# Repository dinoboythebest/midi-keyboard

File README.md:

# midi-keyboard
A musical keyboard madde by tamilore adeabjo
added 3 led and 3 buttons on the bottom , though no graphics.
made a cool lighting design with the 7 keys provided and used the XIAO ESP32-S3 BOard

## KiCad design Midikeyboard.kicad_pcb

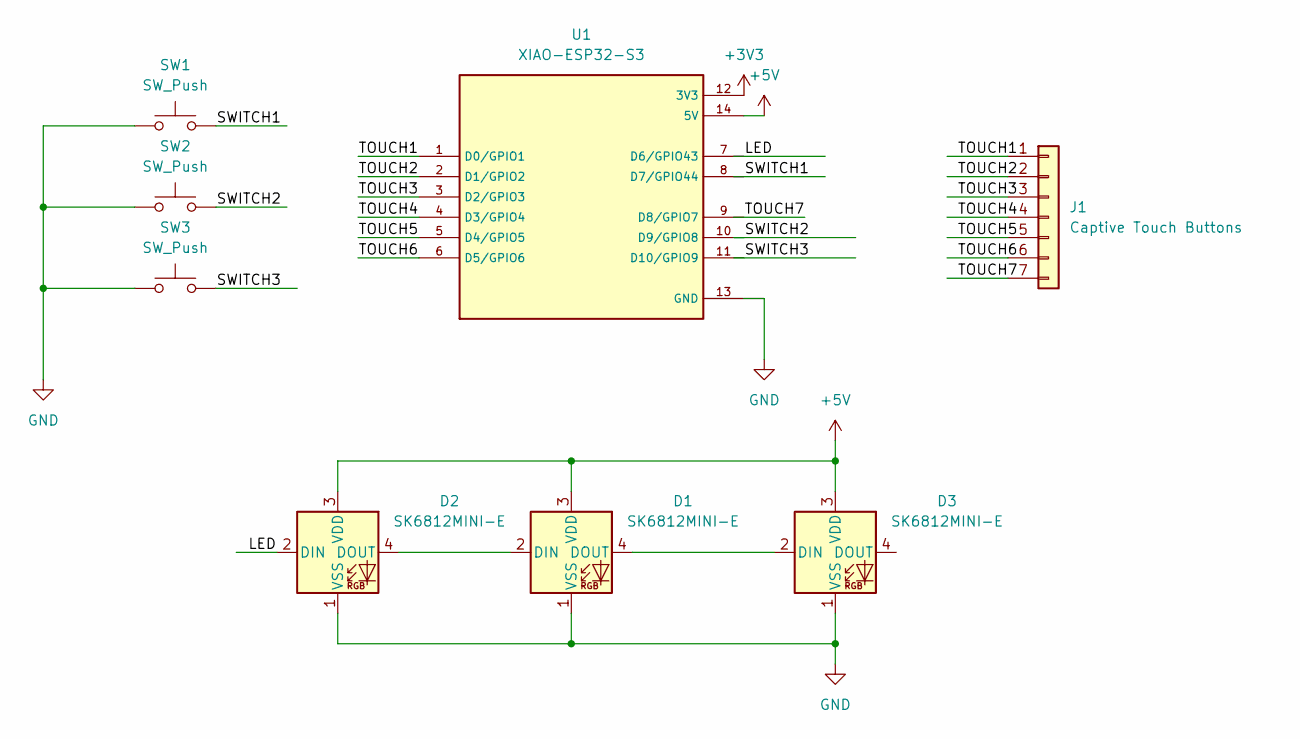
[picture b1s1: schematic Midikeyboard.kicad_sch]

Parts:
D1, D2, D3: SK6812MINI-E; LED_SK6812MINI-E_3.2x2.8mm_P1.5mm_ReverseMount
J1: Captive Touch Buttons; Lighting_key_thing
SW1, SW2, SW3: SW_Push; Kailh Choc Low-Profile Switches
U1: XIAO-ESP32-S3; XIAO ESP32-S3; PARTREV April 22nd, 2026

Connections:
+3V3: U1.12 (3V3)
+5V: D1.3 (VDD), D2.3 (VDD), D3.3 (VDD), U1.14 (5V)
/LED: D2.2 (DIN), U1.7 (D6/GPIO43)
/SWITCH1: SW1.2, U1.8 (D7/GPIO44)
/SWITCH2: SW2.2, U1.10 (D9/GPIO8)
/SWITCH3: SW3.2, U1.11 (D10/GPIO9)
/TOUCH1: J1.1, U1.1 (D0/GPIO1)
/TOUCH2: J1.2, U1.2 (D1/GPIO2)
/TOUCH3: J1.3, U1.3 (D2/GPIO3)
/TOUCH4: J1.4, U1.4 (D3/GPIO4)
/TOUCH5: J1.5, U1.5 (D4/GPIO5)
/TOUCH6: J1.6, U1.6 (D5/GPIO6)
/TOUCH7: J1.7, U1.9 (D8/GPIO7)
GND: D1.1 (VSS), D2.1 (VSS), D3.1 (VSS), SW1.1, SW2.1, SW3.1, U1.13 (GND)
unnamed: D1.2 (DIN), D2.4 (DOUT)
unnamed: D1.4 (DOUT), D3.2 (DIN)

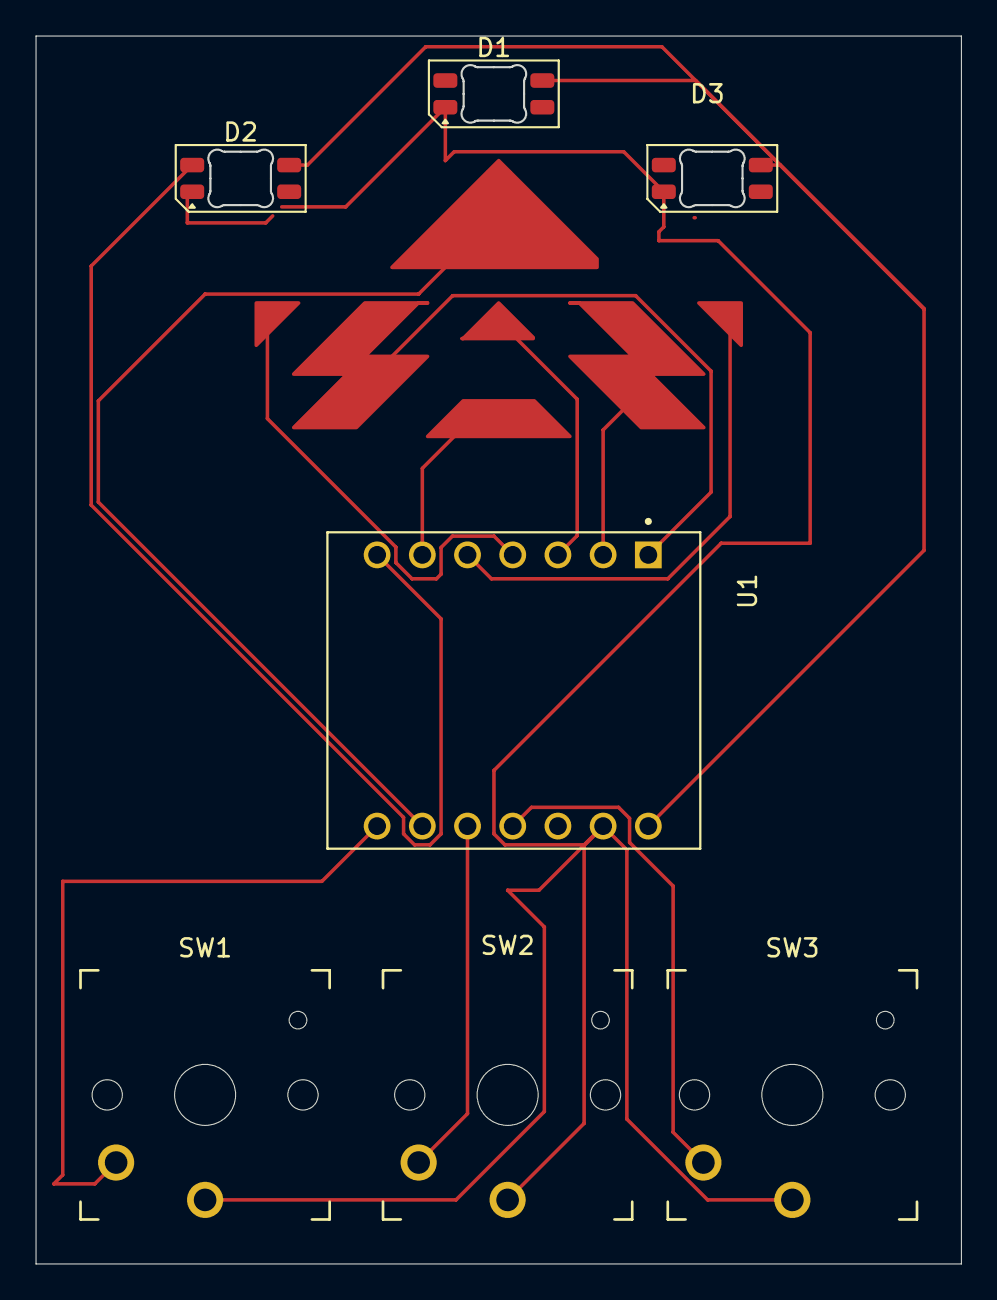
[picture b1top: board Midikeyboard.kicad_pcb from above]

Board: 2 copper layers, 52.0 x 69.0 mm, 8 parts (0 on the bottom side), 15 nets.

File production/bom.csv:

Designator,Footprint,Quantity,Value,LCSC Part #
"D1, D2, D3",LED_SK6812MINI-E_3.2x2.8mm_P1.5mm_ReverseMount,3,SK6812MINI-E,
J1,Lighting_key_thing,1,Captive Touch Buttons,
"SW1, SW2, SW3",Kailh Choc Low-Profile Switches,3,SW_Push,
U1,XIAO ESP32-S3,1,XIAO-ESP32-S3,
